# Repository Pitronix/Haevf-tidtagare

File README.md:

# Hävf-Timer
 En hävf tidtagare i kreditkortsformat, perfekt när man vill utmana sina vänner eller göra övningshävf då det även finns en inbyggd självstart funktion.
 ## Användning:
1. Tidtagaren sätts i **tävlingsmod** när den vänstra knappen trycks ner en gång. Tidtagningen startas och stoppas med ett slag på bordet. Nollställning görs på den vänstra knappen.
2. Tidtagaren sätts i **träningsmod** genom att hålla inne den vänsta knappen. En nedräkning från 5 sekunder startas och tiden börjar räkna upp automatisk. Tidtagningen stoppas med ett slag på bordet och nollställs med ett tryck på den vänstra knappen.

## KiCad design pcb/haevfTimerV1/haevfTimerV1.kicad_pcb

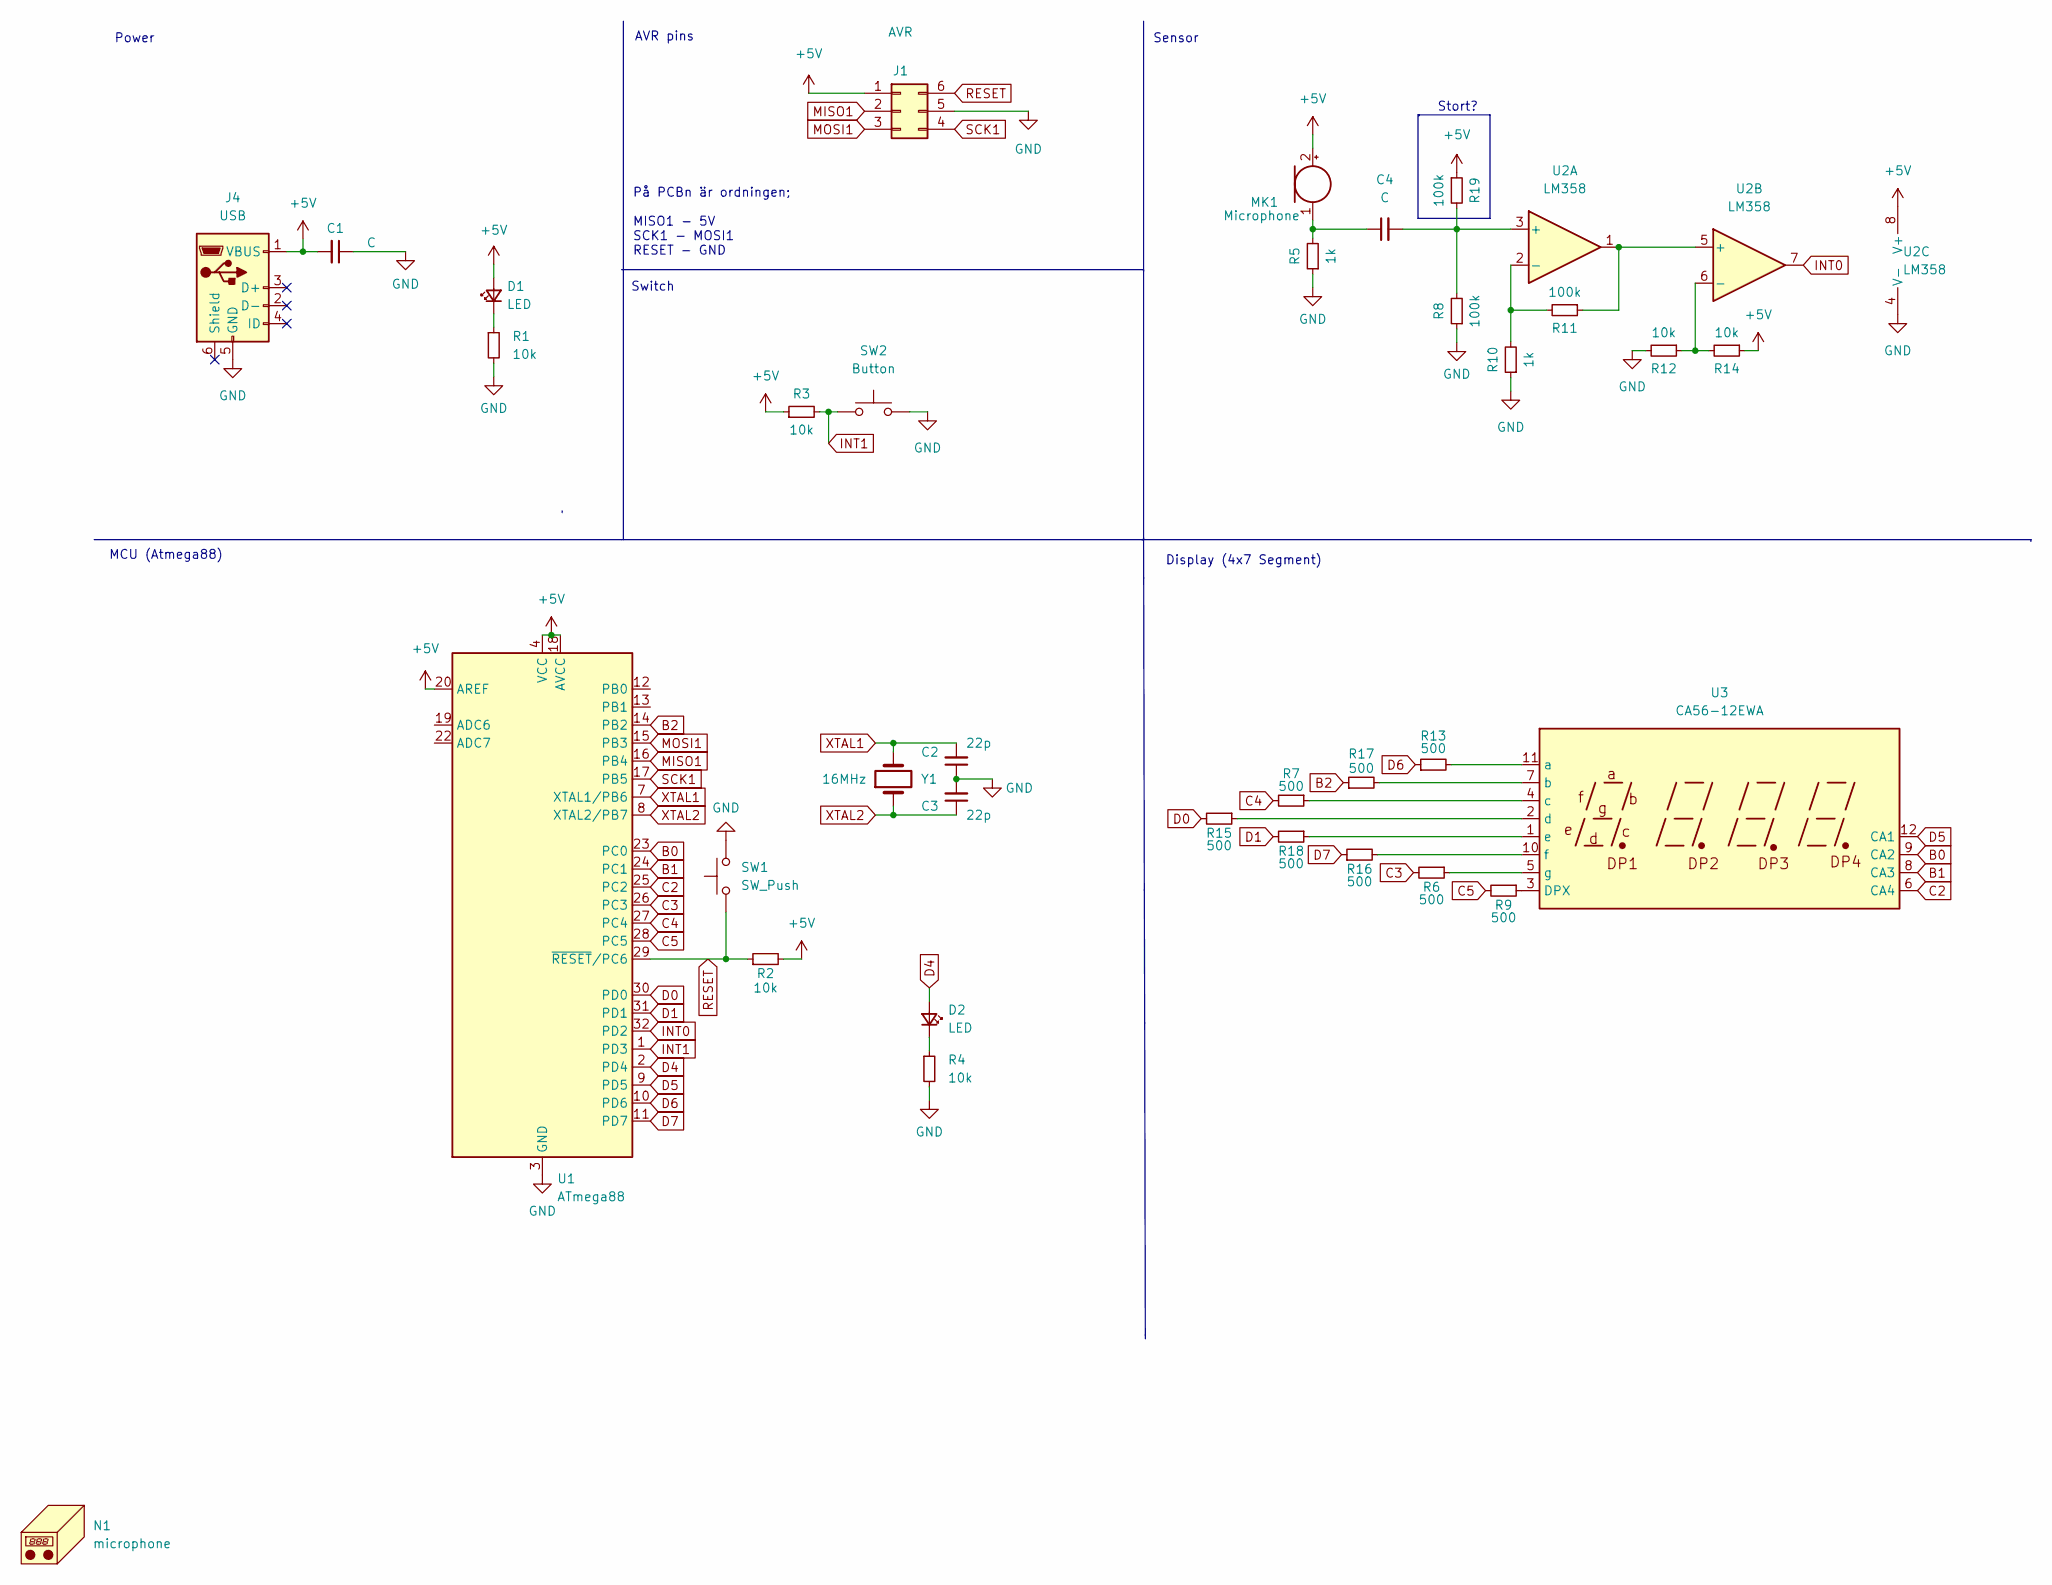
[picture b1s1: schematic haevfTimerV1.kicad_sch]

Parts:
C1, C4: C; C_0603_1608Metric
C2, C3: 22p; C_0603_1608Metric
D1, D2: LED; LED_0603_1608Metric
J1: AVR; PinHeader_2x03_P2.54mm_Vertical
J4: USB; USB_Mini-B_Lumberg_2486_01_Horizontal
MK1: Microphone; SolderWire-0.5sqmm_1x02_P4.6mm_D0.9mm_OD2.1mm
N1: microphone; Symbol_CC-PublicDomain_CopperTop_Small
R1, R2, R3, R4, R12, R14: 10k; R_0603_1608Metric
R5, R10: 1k; R_0603_1608Metric
R6, R7, R9, R13, R15, R16, R17, R18: 500; R_0603_1608Metric
R8, R11, R19: 100k; R_0603_1608Metric
SW1: SW_Push; SW_SPST_B3S-1000
SW2: Button; SW_SPST_B3S-1000
U1: ATmega88; TQFP-32_7x7mm_P0.8mm
U2: LM358; SOIC-8-1EP_3.9x4.9mm_P1.27mm_EP2.29x3mm
U3: CA56-12EWA
Y1: 16MHz; Crystal_SMD_HC49-SD

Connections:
+5V: C1.2, D1.2 (A), J1.1, J4.1 (VBUS), MK1.2 (+), R2.2, R3.1, R14.1, R19.1, U1.4 (VCC), U1.6 (VCC), U1.18 (AVCC), U1.20 (AREF), U2.8 (V+)
B0: U1.23 (PC0), U3.9 (CA2)
B1: U1.24 (PC1), U3.8 (CA3)
B2: R17.1, U1.14 (PB2)
C2: U1.25 (PC2), U3.6 (CA4)
C3: R6.2, U1.26 (PC3)
C4: R7.2, U1.27 (PC4)
C5: R9.2, U1.28 (PC5)
D0: R15.2, U1.30 (PD0)
D1: R18.2, U1.31 (PD1)
D4: D2.2 (A), U1.2 (PD4)
D5: U1.9 (PD5), U3.12 (CA1)
D6: R13.1, U1.10 (PD6)
D7: R16.1, U1.11 (PD7)
GND: C1.1, C2.1, C3.2, J1.5, J4.5 (GND), R1.2, R4.2, R5.1, R8.1, R10.1, R12.2, SW1.2, SW2.2, U1.3 (GND), U1.5 (GND), U1.21 (GND), U2.4 (V-)
INT0: U1.32 (PD2), U2.7
INT1: R3.2, SW2.1, U1.1 (PD3)
MISO1: J1.2, U1.16 (PB4)
MOSI1: J1.3, U1.15 (PB3)
unnamed: C4.1, MK1.1 (-), R5.2
unnamed: C4.2, R8.2, R19.2, U2.3 (+)
unnamed: D1.1 (K), R1.1
unnamed: D2.1 (K), R4.1
unnamed: R6.1, U3.5 (g)
unnamed: R7.1, U3.4 (c)
unnamed: R9.1, U3.3 (DPX)
unnamed: R10.2, R11.2, U2.2 (-)
unnamed: R11.1, U2.1, U2.5 (+)
unnamed: R12.1, R14.2, U2.6 (-)
unnamed: R13.2, U3.11 (a)
unnamed: R15.1, U3.2 (d)
unnamed: R16.2, U3.10 (f)
unnamed: R17.2, U3.7 (b)
unnamed: R18.1, U3.1 (e)
RESET: J1.6, R2.1, SW1.1, U1.29 (~RESET/PC6)
SCK1: J1.4, U1.17 (PB5)
XTAL1: C2.2, U1.7 (XTAL1/PB6), Y1.2
XTAL2: C3.1, U1.8 (XTAL2/PB7), Y1.1

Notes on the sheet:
Display (4x7 Segment)
Sensor
Switch
AVR pins
MCU (Atmega88)
Power
Stort?
På PCBn är ordningen; MISO1 - 5V SCK1 - MOSI1 RESET - GND

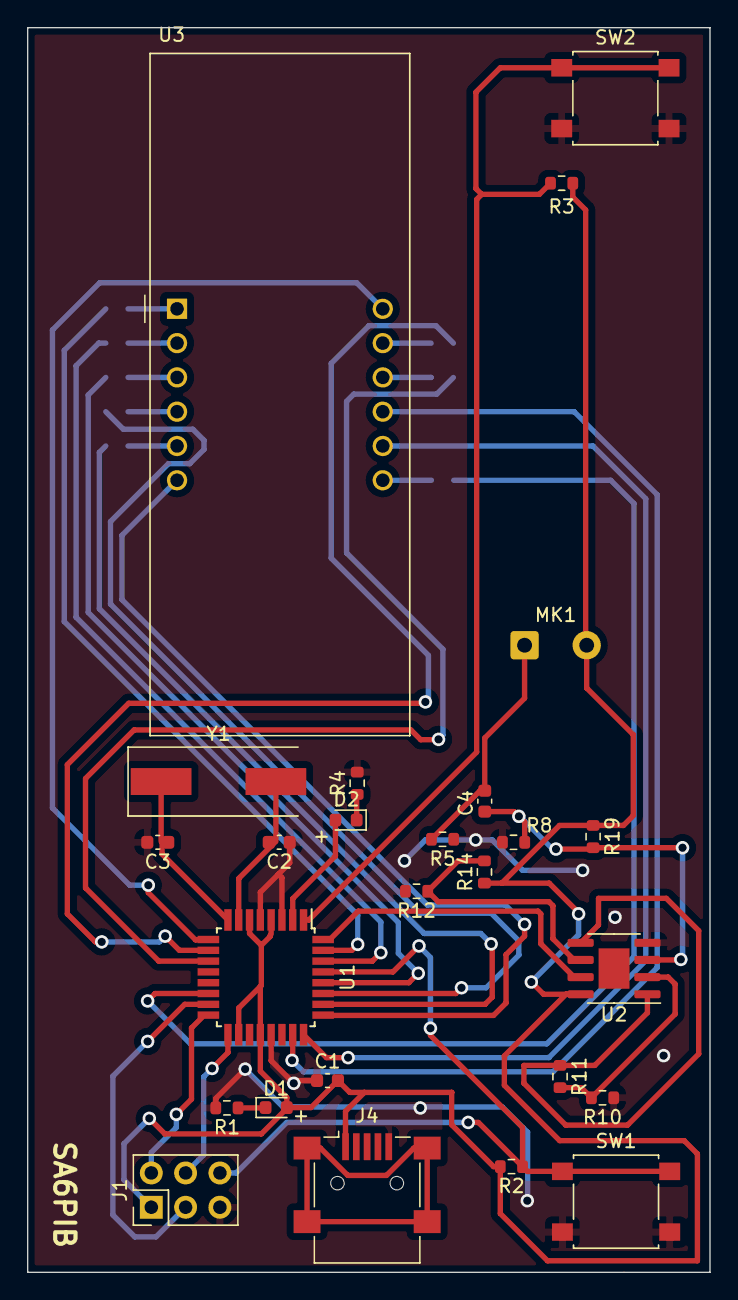
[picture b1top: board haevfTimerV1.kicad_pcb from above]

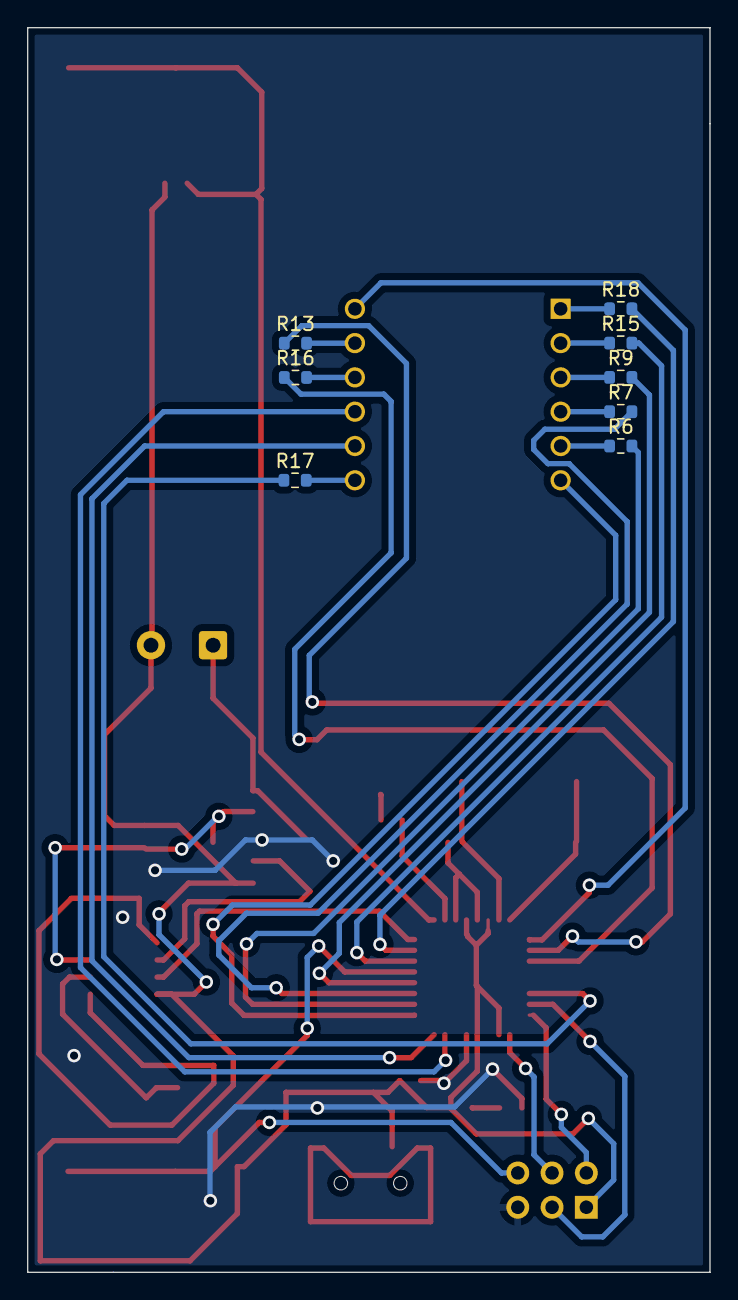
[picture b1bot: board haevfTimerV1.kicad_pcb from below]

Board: 2 copper layers, 50.5 x 92.2 mm, 34 parts (8 on the bottom side), 38 nets.

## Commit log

2022-12-14 Added V1 to repository
2022-12-14 Added code
